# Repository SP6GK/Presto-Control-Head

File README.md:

# Control head for Presto — QO-100 Transverter

**Status: Work in Progress — November 2026**

Control head unit with LCD, encoder, tactile buttons and STM32F411 microcontroller for Presto transverter.

This project includes the schematic and PCB design files, organized under the `ECAD/` directory.
Software and its documentation is in `/Software/SW__0005_PrestoCH_rev_01a//` where `MCU/` includes STM32 project and SCPI commands for remote control. 
`Documents/` includes interactive BOM and .pdf schematic.

## Features
- **Embedded firmware:** STM32F411 microcontroller running C with FreeRTOS.
- **Encoder and 4 tactile buttons** as human-machine interface
- **2.8" TFT LCD** with touchscreen and ILI9341 controller
- **Graphical interface:** Frequency control, configuration menus, and diagnostic information.
- **Remote control:** B.A.S.I.C. (Basic Automated SCPI Interpreter for Controllers) provides serial control through SCPI-like commands.
- **Built-in diagnostics:** Startup and runtime self-tests, error logging, memory integrity checks, and automatic gain control.
- **On board EEPROM:** Stores board identification data and calibration.
- **Calibration tools:** Python scripts and service commands for EEPROM programming and automated calibration.
- **ICSP port:** exposed for easy reprogramming and evaluation

## System and compatibility
This repository contains all documentation for the control head of Presto transverter. Complete system consists also requires:
- **Motherboard** Contains RF signal path and power supplies: 
- **2 x LO Module** LMX2572 LP based local oscillator module

## Project Status

**This project is actively under development and is not yet complete.**
Currently the RF path is under evaluation and characterization.
There was a known issue with ADC pin assignment, fixed with bodge wire. TODO: document fix in project.

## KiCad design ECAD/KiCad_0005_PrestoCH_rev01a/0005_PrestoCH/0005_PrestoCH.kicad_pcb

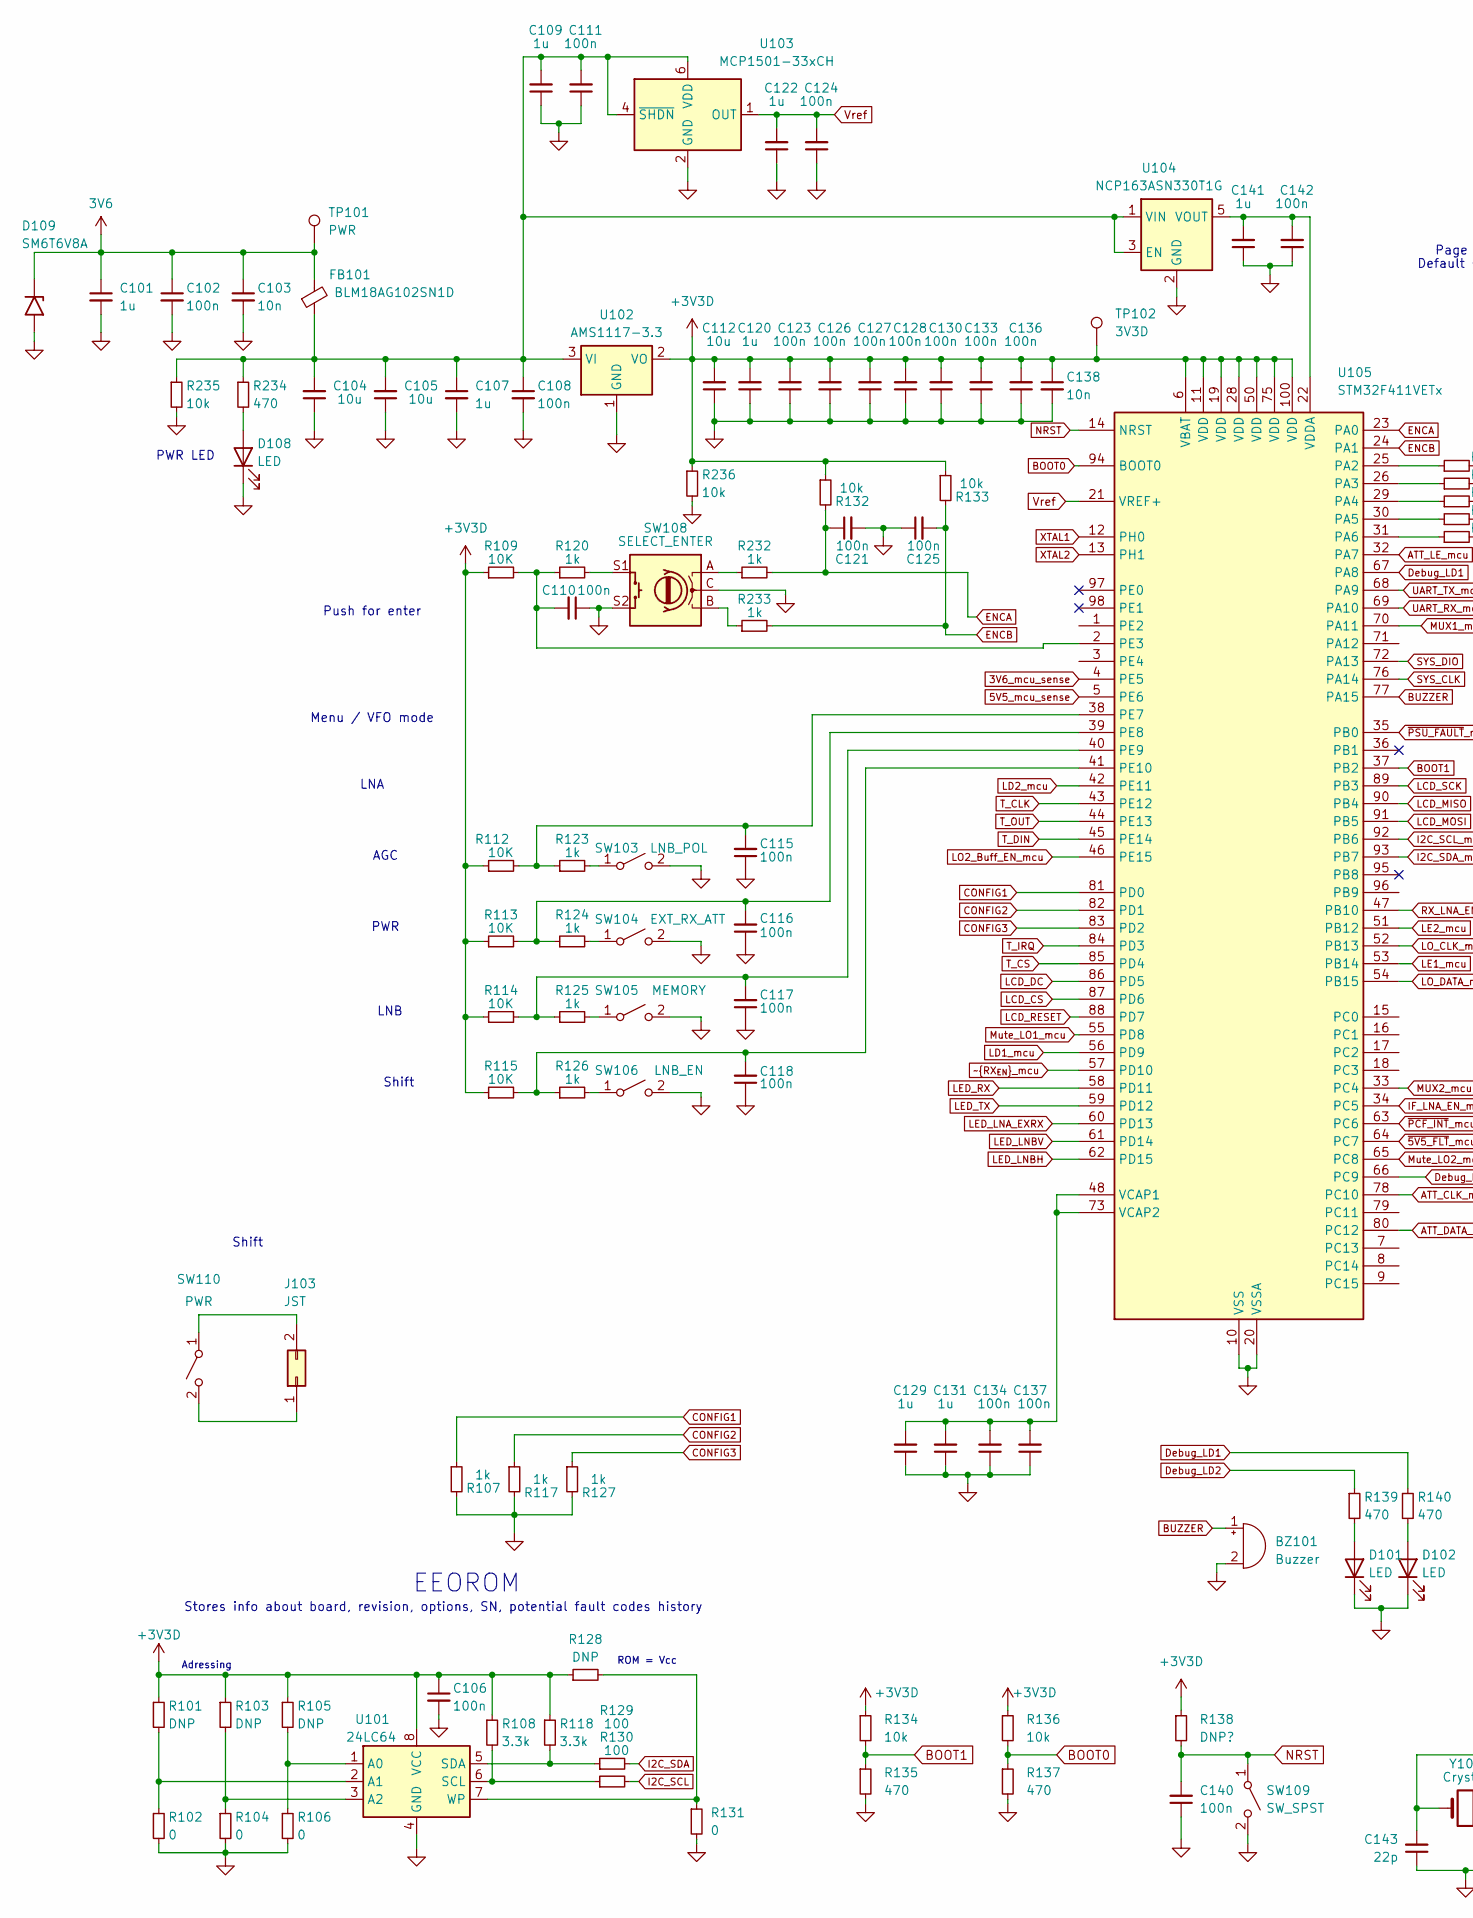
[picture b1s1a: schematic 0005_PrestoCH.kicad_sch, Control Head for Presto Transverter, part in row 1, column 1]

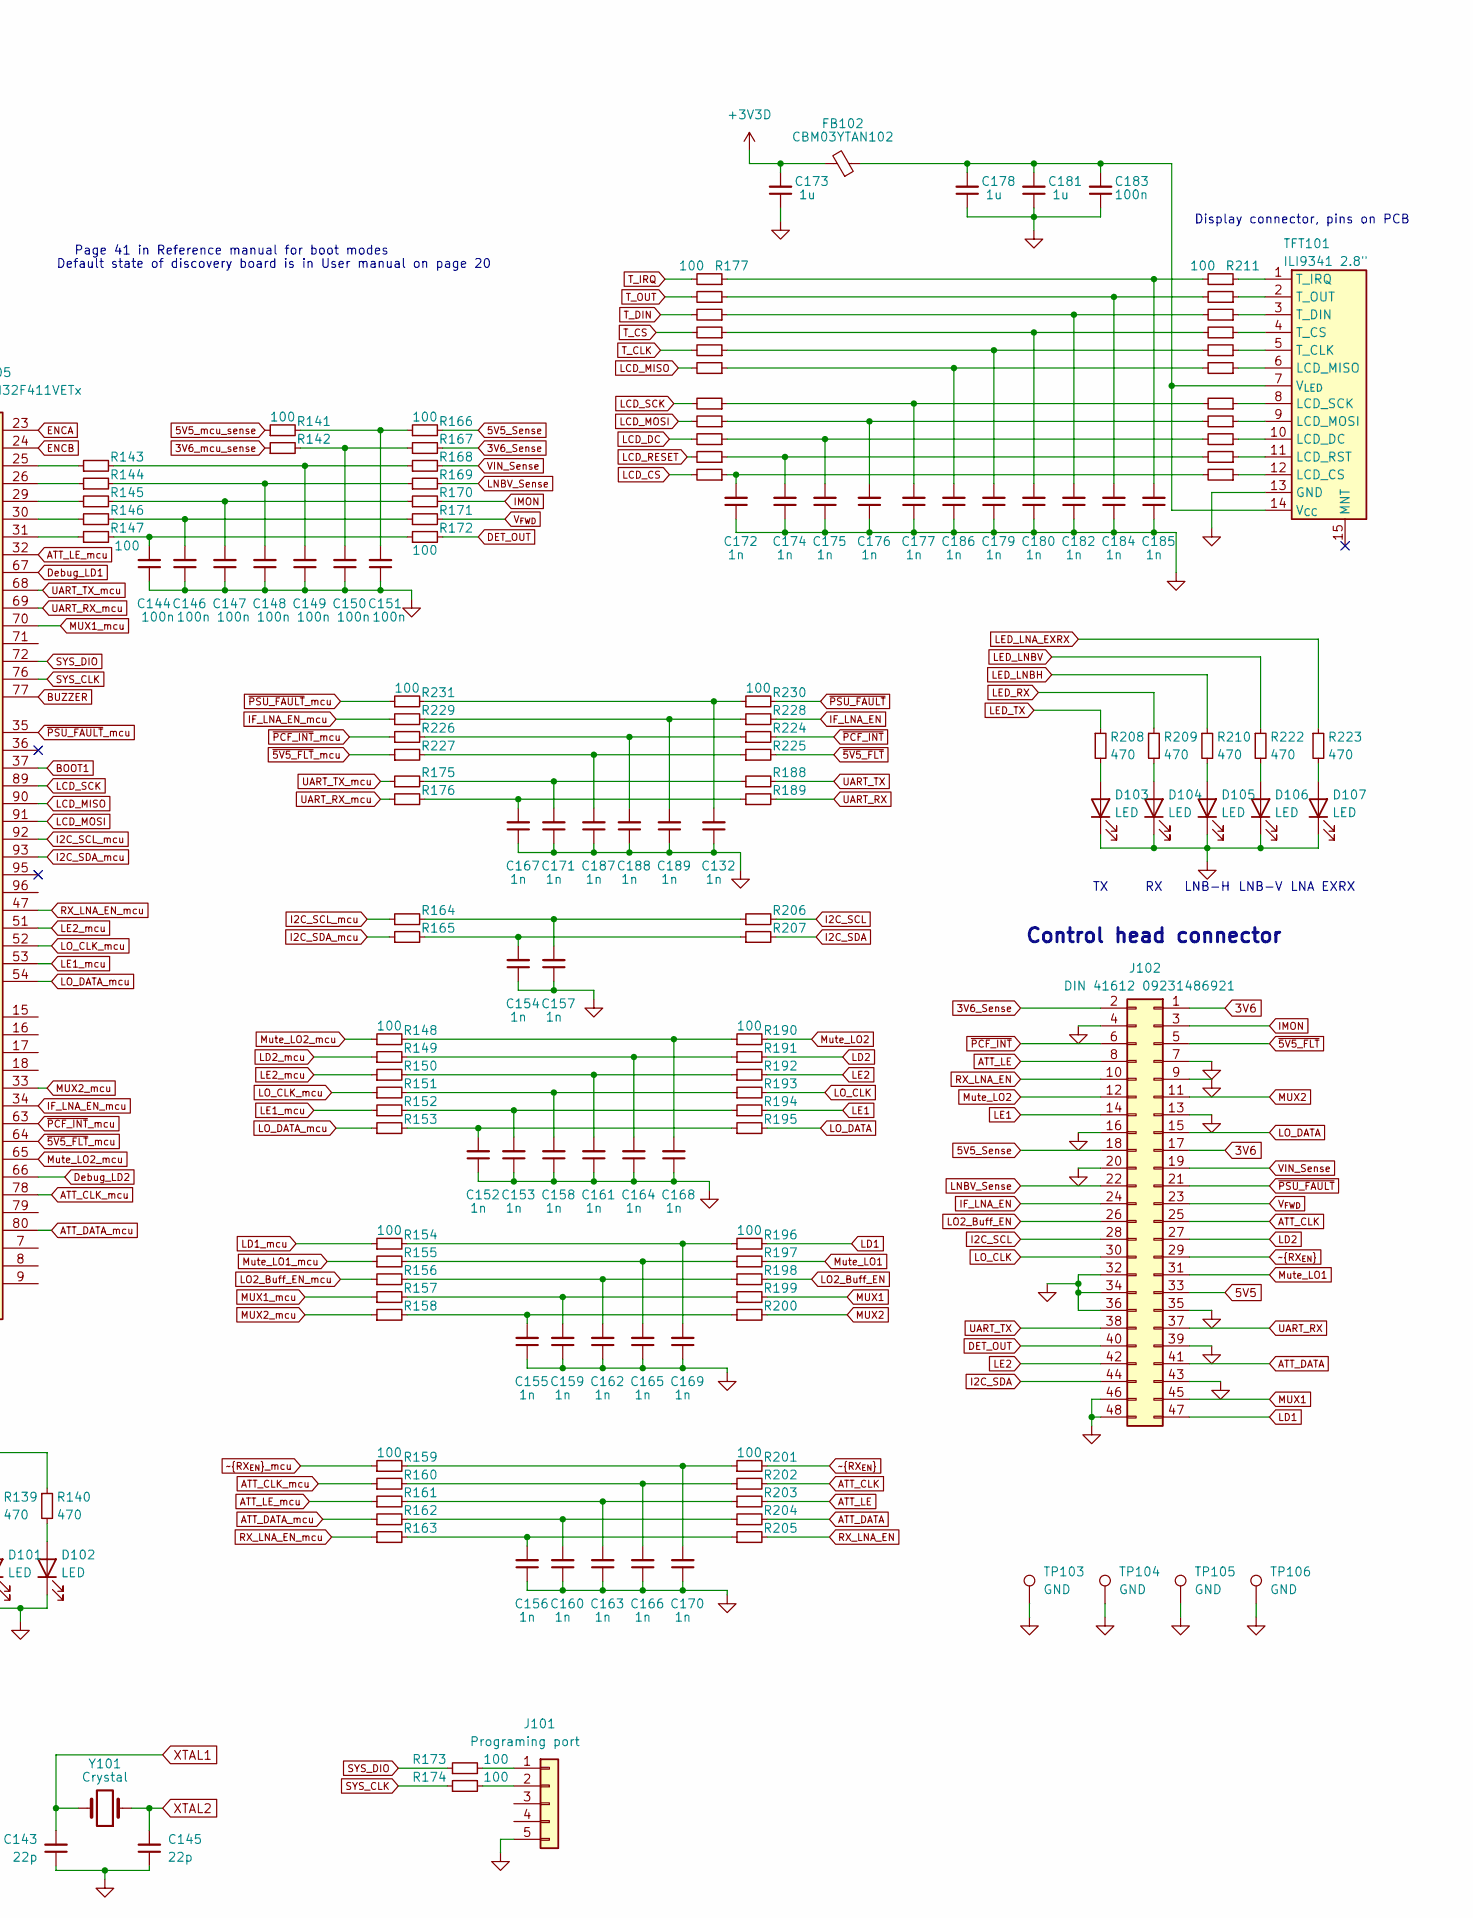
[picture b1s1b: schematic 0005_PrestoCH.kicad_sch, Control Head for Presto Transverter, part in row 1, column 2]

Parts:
BZ101: Buzzer; PinSocket_1x02_P2.54mm_Vertical_SMD_Pin1Right
C101, C107, C109, C120, C122, C129, C131, C141, C173, C178, C181: 1u; C_0805_2012Metric
C102, C106, C108, C110, C111, C115, C116, C117, C118, C121, C123, C124, C125, C126, C127, C128, C130, C133, C134, C136, C137, C140, C142, C144, C146, C147, C148, C149, C150, C151, C183: 100n; C_0603_1608Metric_Pad1.08x0.95mm_HandSolder
C103, C138: 10n; C_0603_1608Metric_Pad1.08x0.95mm_HandSolder
C104, C105, C112: 10u; C_1206_3216Metric
C132, C152, C153, C154, C155, C156, C157, C158, C159, C160, C161, C162, C163, C164, C165, C166, C167, C168, C169, C170, C171, C172, C174, C175, C176, C177, C179, C180, C182, C184, C185, C186, C187, C188, C189: 1n; C_0603_1608Metric_Pad1.08x0.95mm_HandSolder
C143, C145: 22p; C_0603_1608Metric_Pad1.08x0.95mm_HandSolder
D101, D102, D103, D104, D105, D106, D107, D108: LED; D_0805_2012Metric_Pad1.15x1.40mm_HandSolder
D109: SM6T6V8A; D_SMB
FB101: BLM18AG102SN1D; L_0603_1608Metric_Pad1.05x0.95mm_HandSolder
FB102: CBM03YTAN102; L_0603_1608Metric_Pad1.05x0.95mm_HandSolder
J101: Programing port; PinHeader_1x05_P2.54mm_Vertical_SMD_Pin1Left
J102: DIN 41612 09231486921; DIN_41612_48Pin_90angle_Male_09231486921HARTING
J103: JST; JST_EH_B2B-EH-A_1x02_P2.50mm_Vertical
R101, R103, R105: DNP; R_0805_2012Metric_Pad1.20x1.40mm_HandSolder
R102, R104, R106: 0; R_0805_2012Metric_Pad1.20x1.40mm_HandSolder
R107, R117, R120, R123, R124, R125, R126, R127, R232, R233: 1k; R_0603_1608Metric_Pad0.98x0.95mm_HandSolder
R108, R118: 3.3k; R_0603_1608Metric_Pad0.98x0.95mm_HandSolder
R109, R112, R113, R114, R115: 10K; R_0603_1608Metric_Pad0.98x0.95mm_HandSolder
R128: DNP; R_0603_1608Metric_Pad0.98x0.95mm_HandSolder
R129, R130: 100; R_0603_1608Metric_Pad0.98x0.95mm_HandSolder
R131: 0; R_0603_1608Metric_Pad0.98x0.95mm_HandSolder
R132, R133, R134, R136: 10k; R_0603_1608Metric
R135, R137, R139, R140, R208, R209, R210, R222, R223, R234: 470; R_0603_1608Metric
R138: DNP?; R_0603_1608Metric
R141, R142, R143, R144, R145, R146, R147, R148, R149, R150, R151, R152, R153, R154, R155, R156, R157, R158, R159, R160, R161, R162, R163, R164, R165, R166, R167, R168, R169, R170, R171, R172, R173, R174, R175, R176, R177, R178, R179, R180, R181, R182, R183, R184, R185, R186, R187, R188, R189, R190, R191, R192, R193, R194, R195, R196, R197, R198, R199, R200, R201, R202, R203, R204, R205, R206, R207, R211, R212, R213, R214, R215, R216, R217, R218, R219, R220, R221, R224, R225, R226, R227, R228, R229, R230, R231: 100; R_0603_1608Metric
R235, R236: 10k; R_0805_2012Metric
SW103: LNB_POL; SW_TH_Tactile_Omron_B3F-10xx
SW104: EXT_RX_ATT; SW_TH_Tactile_Omron_B3F-10xx
SW105: MEMORY; SW_TH_Tactile_Omron_B3F-10xx
SW106: LNB_EN; SW_TH_Tactile_Omron_B3F-10xx
SW108: SELECT_ENTER; RotaryEncoder_Alps_EC11E-Switch_Vertical_H20mm
SW109: SW_SPST; SW_Tactile_SPST_NO_Straight_CK_PTS636Sx25SMTRLFS
SW110: PWR; SW_TH_Tactile_Omron_B3F-10xx
TFT101: ILI9341 2.8"; 2.8inch_Displays_ILI9341_Module
TP101: PWR; TestPoint_Pad_2.5x2.5mm
TP102: 3V3D; TestPoint_Pad_2.5x2.5mm
TP103, TP104, TP105, TP106: GND; TestPoint_Loop_D2.50mm_Drill1.85mm
U101: 24LC64; SOIC-8_3.9x4.9mm_P1.27mm
U102: AMS1117-3.3; SOT-223-3_TabPin2
U103: MCP1501-33xCH; SOT-23-6
U104: NCP163ASN330T1G; SOT-23-5
U105: STM32F411VETx; LQFP-100_14x14mm_P0.5mm
Y101: Crystal; Crystal_SMD_7050-4Pin_7.0x5.0mm

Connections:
3V6: C101.1, C102.1, C103.1, D109.1 (A1), FB101.2, J102.1, J102.17, TP101.1
3V6_Sense: J102.2, R167.2
3V6_mcu_sense: R142.1, U105.4 (PE5)
5V5: J102.33
5V5_Sense: J102.18, R166.2
5V5_mcu_sense: R141.1, U105.5 (PE6)
+3V3D: C106.1, C112.2, C120.2, C123.2, C126.2, C127.2, C128.2, C130.2, C133.2, C136.2, C138.1, C173.2, FB102.2, R101.1, R103.1, R105.1, R108.1, R109.1, R112.1, R113.1, R114.1, R115.1, R118.1, R128.1, R132.1, R133.1, R134.1, R136.1, R138.1, R236.1, TP102.1, U101.8 (VCC), U102.2 (VO), U105.6 (VBAT), U105.11 (VDD), U105.19 (VDD), U105.28 (VDD), U105.50 (VDD), U105.75 (VDD), U105.100 (VDD)
ATT_CLK: J102.25, R202.2
ATT_CLK_mcu: R160.1, U105.78 (PC10)
ATT_DATA: J102.41, R204.2
ATT_DATA_mcu: R162.1, U105.80 (PC12)
ATT_LE: J102.8, R203.2
ATT_LE_mcu: R161.1, U105.32 (PA7)
BOOT0: R136.2, R137.1, U105.94 (BOOT0)
BOOT1: R134.2, R135.1, U105.37 (PB2)
BUZZER: BZ101.1 (-), U105.77 (PA15)
CONFIG1: R107.1, U105.81 (PD0)
CONFIG2: R117.1, U105.82 (PD1)
CONFIG3: R127.1, U105.83 (PD2)
DET_OUT: J102.40, R172.2
Debug_LD1: R140.1, U105.67 (PA8)
Debug_LD2: R139.1, U105.66 (PC9)
ENCA: C121.1, R132.2, R232.2, U105.23 (PA0)
ENCB: C125.2, R133.2, R233.2, U105.24 (PA1)
GND: BZ101.2 (+), C101.2, C102.2, C103.2, C104.1, C105.1, C106.2, C107.2, C108.2, C109.1, C110.1, C111.1, C112.1, C115.1, C116.1, C117.1, C118.1, C120.1, C121.2, C122.1, C123.1, C124.1, C125.1, C126.1, C127.1, C128.1, C129.1, C130.1, C131.1, C132.1, C133.1, C134.1, C136.1, C137.1, C138.2, C140.1, C141.1, C142.1, C143.1, C144.1, C145.1, C146.1, C147.1, C148.1, C149.1, C150.1, C151.1, C152.1, C153.1, C154.1, C155.1, C156.1, C157.1, C158.1, C159.1, C160.1, C161.1, C162.1, C163.1, C164.1, C165.1, C166.1, C167.1, C168.1, C169.1, C170.1, C171.1, C172.1, C173.1, C174.1, C175.1, C176.1, C177.1, C178.1, C179.1, C180.1, C181.1, C182.1, C183.1, C184.1, C185.1, C186.1, C187.1, C188.1, C189.1, D101.1 (K), D102.1 (K), D103.1 (K), D104.1 (K), D105.1 (K), D106.1 (K), D107.1 (K), D108.1 (K), D109.2 (A2), J101.5, J102.4, J102.7, J102.9, J102.13, J102.16, J102.20, J102.32, J102.34, J102.35, J102.36, J102.39, J102.43, J102.46, J102.48, R102.2, R104.2, R106.2, R107.2, R117.2, R127.2, R131.2, R135.2, R137.2, R235.2, R236.2, SW103.2 (B), SW104.2 (B), SW105.2 (B), SW106.2 (B), SW108.C, SW108.S2, SW109.2 (B), TFT101.13 (GND), TP103.1, TP104.1, TP105.1, TP106.1, U101.4 (GND), U102.1 (GND), U103.2 (GND), U103.3 (GND), U103.5 (GND), U104.2 (GND), U105.10 (VSS), U105.20 (VSSA), U105.27 (VSS), U105.49 (VSS), U105.74 (VSS), U105.99 (VSS)
I2C_SCL: J102.28, R130.2, R206.2
I2C_SCL_mcu: R164.1, U105.92 (PB6)
I2C_SDA: J102.44, R129.2, R207.2
I2C_SDA_mcu: R165.1, U105.93 (PB7)
IF_LNA_EN: J102.24, R228.2
IF_LNA_EN_mcu: R229.1, U105.34 (PC5)
IMON: J102.3, R170.2
LCD_CS: R187.2, U105.87 (PD6)
LCD_DC: R185.2, U105.86 (PD5)
LCD_MISO: R182.2, U105.90 (PB4)
LCD_MOSI: R184.2, U105.91 (PB5)
LCD_RESET: R186.2, U105.88 (PD7)
LCD_SCK: R183.2, U105.89 (PB3)
LD1: J102.47, R196.2
LD1_mcu: R154.1, U105.56 (PD9)
LD2: J102.27, R191.2
LD2_mcu: R149.1, U105.42 (PE11)
LE1: J102.14, R194.2
LE1_mcu: R152.1, U105.53 (PB14)
LE2: J102.42, R192.2
LE2_mcu: R150.1, U105.51 (PB12)
LED_LNA_EXRX: R223.1, U105.60 (PD13)
LED_LNBH: R210.1, U105.62 (PD15)
LED_LNBV: R222.1, U105.61 (PD14)
LED_RX: R209.1, U105.58 (PD11)
LED_TX: R208.1, U105.59 (PD12)
LNBV_Sense: J102.22, R169.2
LO2_Buff_EN: J102.26, R198.2
LO2_Buff_EN_mcu: R156.1, U105.46 (PE15)
LO_CLK: J102.30, R193.2
LO_CLK_mcu: R151.1, U105.52 (PB13)
LO_DATA: J102.15, R195.2
LO_DATA_mcu: R153.1, U105.54 (PB15)
MUX1: J102.45, R199.2
MUX1_mcu: R157.1, U105.70 (PA11)
MUX2: J102.11, R200.2
MUX2_mcu: R158.1, U105.33 (PC4)
Mute_LO1: J102.31, R197.2
Mute_LO1_mcu: R155.1, U105.55 (PD8)
Mute_LO2: J102.12, R190.2
Mute_LO2_mcu: R148.1, U105.65 (PC8)
NRST: C140.2, R138.2, SW109.1 (A), U105.14 (NRST)
unnamed: C132.2, R230.1, R231.2
unnamed: C144.2, R147.2, R172.1
unnamed: C146.2, R146.2, R171.1
unnamed: C147.2, R145.2, R170.1
unnamed: C148.2, R144.2, R169.1
unnamed: C149.2, R143.2, R168.1
unnamed: C150.2, R142.2, R167.1
unnamed: C151.2, R141.2, R166.1
unnamed: C152.2, R153.2, R195.1
unnamed: C153.2, R152.2, R194.1
unnamed: C154.2, R165.2, R207.1
unnamed: C155.2, R158.2, R200.1
unnamed: C156.2, R163.2, R205.1
unnamed: C157.2, R164.2, R206.1
unnamed: C158.2, R151.2, R193.1
unnamed: C159.2, R157.2, R199.1
unnamed: C160.2, R162.2, R204.1
unnamed: C161.2, R150.2, R192.1
unnamed: C162.2, R156.2, R198.1
unnamed: C163.2, R161.2, R203.1
unnamed: C164.2, R149.2, R191.1
unnamed: C165.2, R155.2, R197.1
unnamed: C166.2, R160.2, R202.1
unnamed: C167.2, R176.2, R189.1
unnamed: C168.2, R148.2, R190.1
unnamed: C169.2, R154.2, R196.1
unnamed: C170.2, R159.2, R201.1
unnamed: C171.2, R175.2, R188.1
unnamed: C172.2, R187.1, R221.2
unnamed: C174.2, R186.1, R220.2
unnamed: C175.2, R185.1, R219.2
unnamed: C176.2, R184.1, R218.2
unnamed: C177.2, R183.1, R217.2
unnamed: C179.2, R181.1, R215.2
unnamed: C180.2, R180.1, R214.2
unnamed: C182.2, R179.1, R213.2
unnamed: C184.2, R178.1, R212.2
unnamed: C185.2, R177.1, R211.2
unnamed: C186.2, R182.1, R216.2
unnamed: C187.2, R225.1, R227.2
unnamed: C188.2, R224.1, R226.2
unnamed: C189.2, R228.1, R229.2
unnamed: D101.2 (A), R139.2
unnamed: D102.2 (A), R140.2
unnamed: D103.2 (A), R208.2
unnamed: D104.2 (A), R209.2
unnamed: D105.2 (A), R210.2
unnamed: D106.2 (A), R222.2
unnamed: D107.2 (A), R223.2
unnamed: D108.2 (A), R234.2
unnamed: J101.1, R173.2
unnamed: J101.2, R174.2
unnamed: J103.1, SW110.2 (B)
unnamed: J103.2, SW110.1 (A)
unnamed: R120.2, SW108.S1
unnamed: R232.1, SW108.A
unnamed: R233.1, SW108.B
unnamed: R123.2, SW103.1 (A)
unnamed: R124.2, SW104.1 (A)
unnamed: R125.2, SW105.1 (A)
unnamed: R126.2, SW106.1 (A)
unnamed: R221.1, TFT101.12 (LCD_CS)
unnamed: R219.1, TFT101.10 (LCD_DC)
unnamed: R216.1, TFT101.6 (LCD_MISO)
unnamed: R218.1, TFT101.9 (LCD_MOSI)
unnamed: R220.1, TFT101.11 (LCD_RST)
unnamed: R217.1, TFT101.8 (LCD_SCK)
unnamed: R215.1, TFT101.5 (T_CLK)
unnamed: R214.1, TFT101.4 (T_CS)
unnamed: R213.1, TFT101.3 (T_DIN)
unnamed: R211.1, TFT101.1 (T_IRQ)
unnamed: R212.1, TFT101.2 (T_OUT)
unnamed: C178.2, C181.2, C183.2, FB102.1, TFT101.7 (V_{LED}), TFT101.14 (V_{CC})
unnamed: R105.2, R106.1, U101.1 (A0)
unnamed: R101.2, R102.1, U101.2 (A1)
unnamed: R103.2, R104.1, U101.3 (A2)
unnamed: R108.2, R130.1, U101.6 (SCL)
unnamed: R118.2, R129.1, U101.5 (SDA)
unnamed: R128.2, R131.1, U101.7 (WP)
unnamed: C104.2, C105.2, C107.1, C108.1, C109.2, C111.2, FB101.1, R234.1, R235.1, U102.3 (VI), U103.4 (~SHDN), U103.6 (VDD), U104.1 (VIN), U104.3 (EN)
unnamed: C141.2, C142.2, U104.5 (VOUT), U105.22 (VDDA)
unnamed: R143.1, U105.25 (PA2)
unnamed: R144.1, U105.26 (PA3)
unnamed: R145.1, U105.29 (PA4)
unnamed: R146.1, U105.30 (PA5)
unnamed: R147.1, U105.31 (PA6)
unnamed: C110.2, R109.2, R120.1, U105.2 (PE3)
unnamed: C115.2, R112.2, R123.1, U105.38 (PE7)
unnamed: C116.2, R113.2, R124.1, U105.39 (PE8)
unnamed: C117.2, R114.2, R125.1, U105.40 (PE9)
unnamed: C118.2, R115.2, R126.1, U105.41 (PE10)
unnamed: C129.2, C131.2, C134.2, C137.2, U105.48 (VCAP1), U105.73 (VCAP2)
RX_LNA_EN: J102.10, R205.2
RX_LNA_EN_mcu: R163.1, U105.47 (PB10)
SYS_CLK: R174.1, U105.76 (PA14)
SYS_DIO: R173.1, U105.72 (PA13)
T_CLK: R181.2, U105.43 (PE12)
T_CS: R180.2, U105.85 (PD4)
T_DIN: R179.2, U105.45 (PE14)
T_IRQ: R177.2, U105.84 (PD3)
T_OUT: R178.2, U105.44 (PE13)
UART_RX: J102.37, R189.2
UART_RX_mcu: R176.1, U105.69 (PA10)
UART_TX: J102.38, R188.2
UART_TX_mcu: R175.1, U105.68 (PA9)
VIN_Sense: J102.19, R168.2
V_{FWD}: J102.23, R171.2
Vref: C122.2, C124.2, U103.1 (OUT), U105.21 (VREF+)
XTAL1: C143.2, U105.12 (PH0), Y101.2
XTAL2: C145.2, U105.13 (PH1), Y101.1
~5V5_FLT: J102.5, R225.2
~5V5_FLT_mcu: R227.1, U105.64 (PC7)
~PCF_INT: J102.6, R224.2
~PCF_INT_mcu: R226.1, U105.63 (PC6)
~PSU_FAULT: J102.21, R230.2
~PSU_FAULT_mcu: R231.1, U105.35 (PB0)
~RX_{EN}: J102.29, R201.2
~RX_{EN}_mcu: R159.1, U105.57 (PD10)

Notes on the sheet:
Default state of discovery board is in User manual on page 20
Push for enter
Adressing
Page 41 in Reference manual for boot modes
AGC
Display connector, pins on PCB
Control head connector
LNA
LNB-H
Menu / VFO mode
EEOROM
PWR
PWR LED
Stores info about board, revision, options, SN, potential fault codes history
LNB-V
LNB
ROM = Vcc
Shift
LNA EXRX

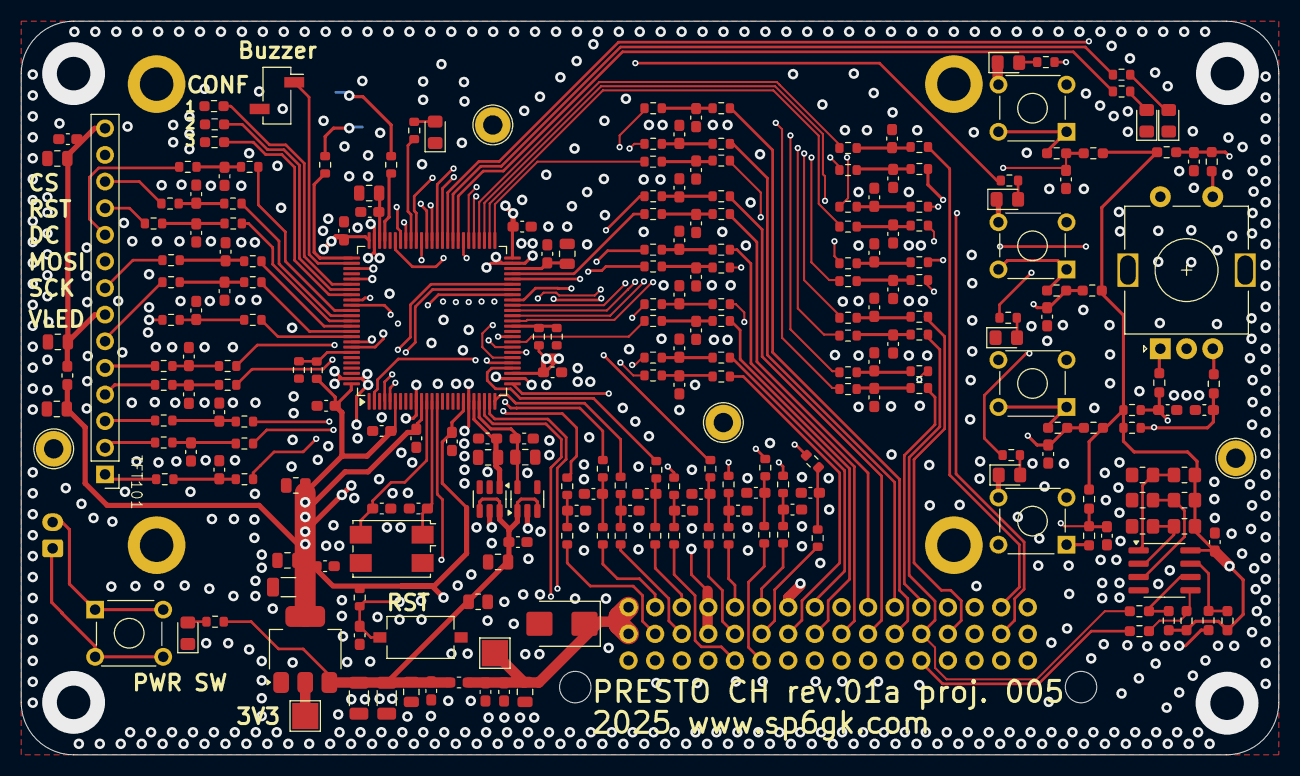
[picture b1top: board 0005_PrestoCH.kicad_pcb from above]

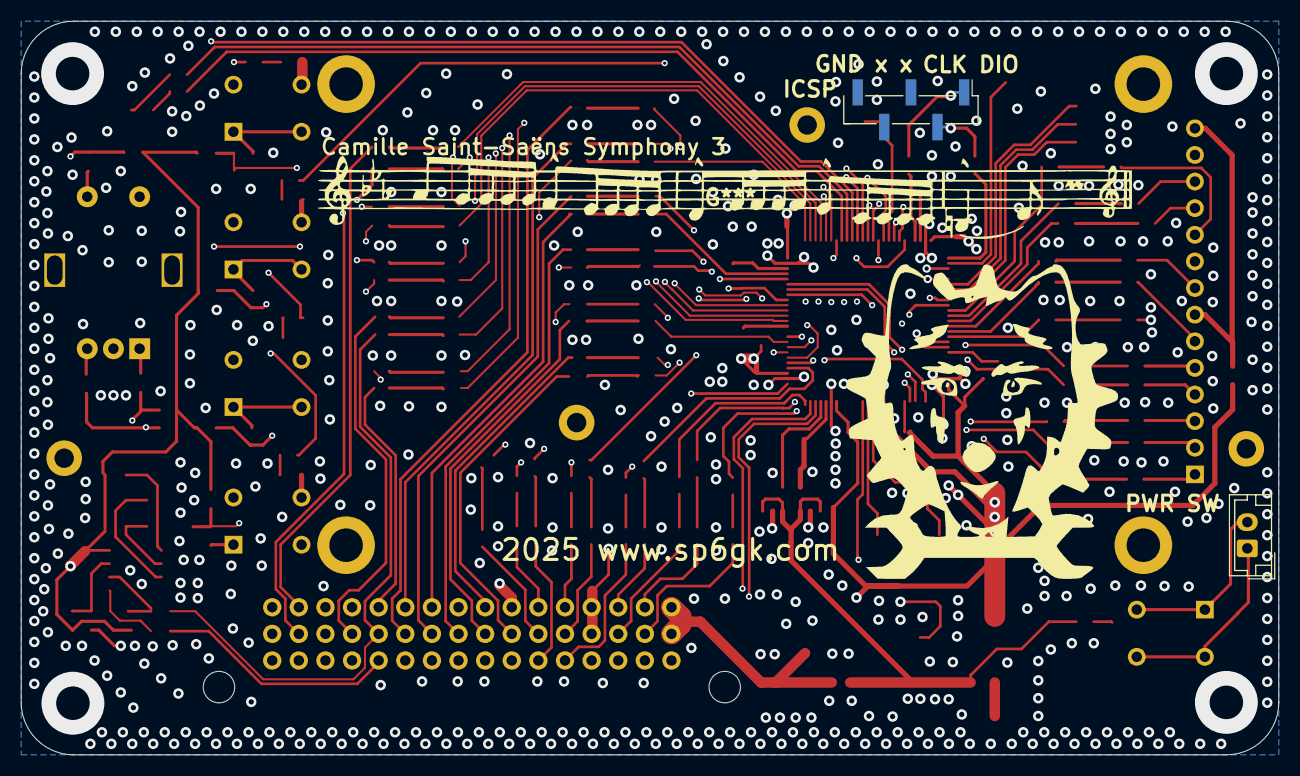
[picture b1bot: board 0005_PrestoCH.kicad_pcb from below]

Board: 4 copper layers, 120.0 x 70.0 mm, 249 parts (2 on the bottom side), 184 nets.

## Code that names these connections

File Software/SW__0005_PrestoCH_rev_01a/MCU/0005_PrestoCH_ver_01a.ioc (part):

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Mcu.Name=STM32F411V(C-E)Tx
Mcu.Package=LQFP100
Mcu.UserName=STM32F411VETx
PA0-WKUP.Signal=S_TIM2_CH1_ETR
PA1.Signal=S_TIM2_CH2
PA10.Mode=Asynchronous
PA10.Signal=USART1_RX
PA11.GPIOParameters=GPIO_Label
PA11.GPIO_Label=LO1_LD
PA11.Signal=GPIO_Input
PA13.Mode=Serial_Wire
PA13.Signal=SYS_JTMS-SWDIO
PA14.Mode=Serial_Wire
PA14.Signal=SYS_JTCK-SWCLK
PA15.GPIOParameters=GPIO_Label
PA15.GPIO_Label=Buzzer
PA15.Signal=GPIO_Output
PA2.Signal=ADCx_IN2
PA3.Signal=ADCx_IN3
PA4.Signal=ADCx_IN4
PA5.Signal=ADCx_IN5
PA6.Signal=ADCx_IN6
PA7.GPIOParameters=GPIO_Label
PA7.GPIO_Label=ATT_LE
PA7.Signal=GPIO_Output
PA8.GPIOParameters=GPIO_Label
PA8.GPIO_Label=LED0
PA8.Signal=GPIO_Output
PA9.Mode=Asynchronous
PA9.Signal=USART1_TX
PB0.GPIOParameters=GPIO_Label
PB0.GPIO_Label=PSU_FLT
PB0.Signal=GPIO_Input
PB10.GPIOParameters=GPIO_Label
PB10.GPIO_Label=RX_LNA_EN
PB10.Signal=GPIO_Output
PB12.GPIOParameters=GPIO_Label
PB12.GPIO_Label=LO2_CS
PB12.Signal=GPIO_Output
PB13.Mode=TX_Only_Simplex_Unidirect_Master
PB13.Signal=SPI2_SCK
PB14.GPIOParameters=GPIO_Label
PB14.GPIO_Label=LO1_CS
PB14.Signal=GPIO_Output
PB15.Mode=TX_Only_Simplex_Unidirect_Master
PB15.Signal=SPI2_MOSI
PB3.Mode=Full_Duplex_Master
PB3.Signal=SPI1_SCK
PB4.Mode=Full_Duplex_Master
PB4.Signal=SPI1_MISO
PB5.Mode=Full_Duplex_Master
PB5.Signal=SPI1_MOSI
PB6.Mode=I2C
PB6.Signal=I2C1_SCL
PB7.Mode=I2C
PB7.Signal=I2C1_SDA
PB9.Signal=S_TIM4_CH4
PC10.Mode=TX_Only_Simplex_Unidirect_Master
PC10.Signal=SPI3_SCK
PC12.Mode=TX_Only_Simplex_Unidirect_Master
PC12.Signal=SPI3_MOSI
PC14-OSC32_IN.GPIOParameters=GPIO_Label
PC14-OSC32_IN.GPIO_Label=LED5
PC14-OSC32_IN.Signal=GPIO_Output
PC2.Signal=ADCx_IN12
PC3.Signal=ADCx_IN13
PC4.GPIOParameters=GPIO_Label
PC4.GPIO_Label=LO2_LD
PC4.Signal=GPIO_Input
PC5.GPIOParameters=GPIO_Label
PC5.GPIO_Label=IF_LNA_EN
PC5.Signal=GPIO_Output
PC6.GPIOParameters=GPIO_Label,GPIO_ModeDefaultEXTI
PC6.GPIO_Label=PCF_INT
PC6.GPIO_ModeDefaultEXTI=GPIO_MODE_IT_FALLING
PC6.Signal=GPXTI6
PC7.GPIOParameters=GPIO_Label
PC7.GPIO_Label=FLT_5V5
PC7.Signal=GPIO_Input
PC8.GPIOParameters=GPIO_Label
PC8.GPIO_Label=LO2_CE
PC8.Signal=GPIO_Output
PC9.GPIOParameters=GPIO_Label
PC9.GPIO_Label=LED1
PC9.Signal=GPIO_Output
PD10.GPIOParameters=GPIO_Label
PD10.GPIO_Label=RX_EN
PD10.Signal=GPIO_Output
PD11.GPIOParameters=GPIO_Label
PD11.GPIO_Label=LED_RX
PD11.Signal=GPIO_Output
PD12.GPIOParameters=GPIO_Label
PD12.GPIO_Label=LED_TX
PD12.Signal=GPIO_Output
PD13.GPIOParameters=GPIO_Label
PD13.GPIO_Label=LED4
PD13.Signal=GPIO_Output
PD14.GPIOParameters=GPIO_Label
PD14.GPIO_Label=LED3
PD14.Signal=GPIO_Output
PD15.GPIOParameters=GPIO_Label
PD15.GPIO_Label=LED2
PD15.Signal=GPIO_Output
PD3.GPIOParameters=GPIO_Label
PD3.GPIO_Label=TOUCH_IRQ
PD3.Signal=GPXTI3
PD4.GPIOParameters=GPIO_Label
PD4.GPIO_Label=TOUCH_CS
PD4.Signal=GPIO_Output
PD5.GPIOParameters=GPIO_Label
PD5.GPIO_Label=TFT_DC
PD5.Signal=GPIO_Output
PD6.GPIOParameters=GPIO_Label
PD6.GPIO_Label=TFT_CS
PD6.Signal=GPIO_Output
PD7.GPIOParameters=GPIO_Label
PD7.GPIO_Label=TFT_RESET
PD7.Signal=GPIO_Output
PD8.GPIOParameters=GPIO_Label
PD8.GPIO_Label=LO1_CE
PD8.Signal=GPIO_Output
PE10.GPIOParameters=GPIO_ModeDefaultEXTI
PE10.GPIO_ModeDefaultEXTI=GPIO_MODE_IT_FALLING
PE10.Signal=GPXTI10
PE15.GPIOParameters=GPIO_Label
PE15.GPIO_Label=LO2_Buf_EN
PE15.Signal=GPIO_Output
PE7.GPIOParameters=GPIO_ModeDefaultEXTI
PE7.GPIO_ModeDefaultEXTI=GPIO_MODE_IT_FALLING
PE7.Signal=GPXTI7
PE8.GPIOParameters=GPIO_ModeDefaultEXTI
PE8.GPIO_ModeDefaultEXTI=GPIO_MODE_IT_FALLING
PE8.Signal=GPXTI8
PE9.GPIOParameters=GPIO_ModeDefaultEXTI
PE9.GPIO_ModeDefaultEXTI=GPIO_MODE_IT_FALLING
PE9.Signal=GPXTI9
RCC.HSE_VALUE=25000000
RCC.SYSCLKFreq_VALUE=100000000
RCC.SYSCLKSource=RCC_SYSCLKSOURCE_PLLCLK
board=custom
